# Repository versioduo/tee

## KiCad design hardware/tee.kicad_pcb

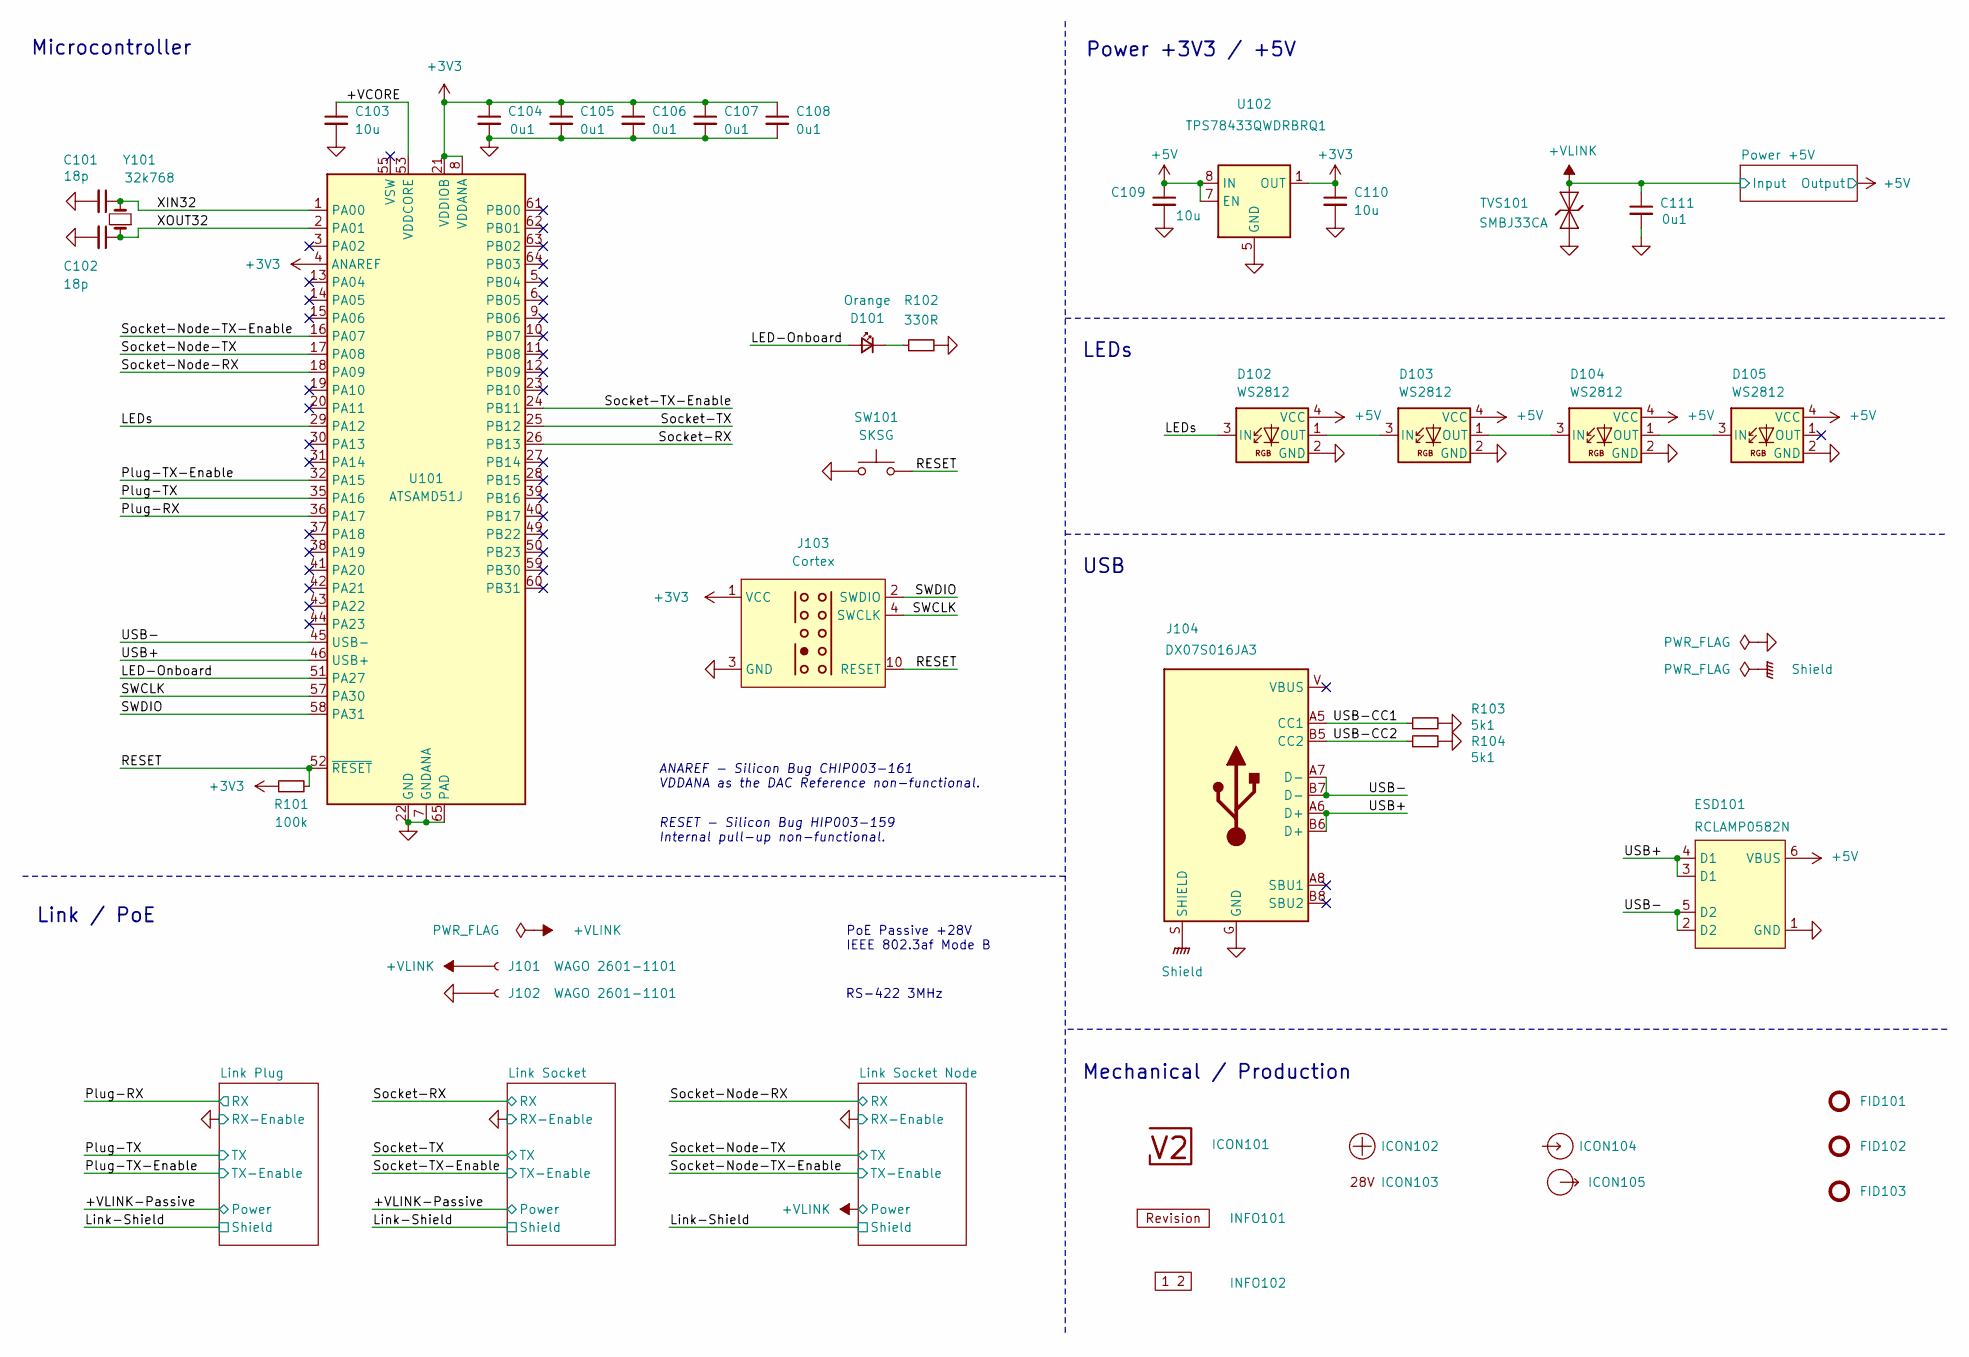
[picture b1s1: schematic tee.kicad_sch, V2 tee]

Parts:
C101, C102: 18p; C_1608; Rating 50V; Mouser 810-CGA3E2C0G1H180J
C103: 10u; C_1608; Rating 10V; Mouser 810-C1608X6S1A106M
C104, C105, C106, C107, C108, C111: 0u1; C_1608; Rating 50V; Mouser 810-CGA3E2X7R1H104MA
C109, C110: 10u; C_2012; Rating 25V; Mouser 810-C2012X5R1E106K
D101: Orange; LED_1608; Rating 605nm; Mouser 755-SML-D12D1WT86
D102, D103, D104, D105: WS2812; WS2812-2020; Rating 15mA; LCSC C965555
ESD101: RCLAMP0582N; SLP1210N6; Rating 20kV; Mouser 947-RCLAMP0582N.TCT
FID101, FID102, FID103: Fiducial_Paste; Fiducial_0.5mm_Mask1mm_Paste
ICON101: V2-logo; Logo_Small
ICON102: Plus; Plus_Small
ICON103: 28V
ICON104: Arrow_In
ICON105: Arrow_Out
INFO101: Revision
INFO102: Layer_Numbers-4
J101, J102: WAGO 2601-1101; 2601-1101; Rating 17.5A
J103: Cortex
J104: DX07S016JA3; JAE_DX07S016JA3; Rating USB2.0; Mouser 656-DX07S016JA3R1500
R101: 100k; R_1608; Rating 100mW; Mouser 71-CRCW0603100KFKEAC
R102: 330R; R_1608; Rating 100mW; Mouser 71-CRCW0603330RFKEAC
R103, R104: 5k1; R_1608; Rating 100mW; Mouser 71-CRCW06035K10FKEAC
SW101: SKSG; Rating 1.6N; Mouser 688-SKSGACE010
TVS101: SMBJ33CA; D_SMB; Rating 33V; Mouser 652-SMBJ33CA-Q
U101: ATSAMD51J; QFN-64-1EP_9x9mm_P0.5mm_EP4.8x4.8mm_ThermalVias; Rating Cortex-M4F; Mouser 556-ATSAMD51J19AMU
U102: TPS78433QWDRBRQ1; VSON-8-1_3x3mm_P0.65_EP1.65x2.4mm; Rating 300mA; Mouser 595-TPS78433QWDRBRQ1
Y101: 32k768; Crystal_SMD_3215-2Pin_3.2x1.5mm; Rating 10ppm; Mouser 815-ABS0716632.768KT

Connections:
+3V3: C104.1, C105.1, C106.1, C107.1, C108.1, C110.1, J103.1 (VCC), R101.1, U101.4 (ANAREF), U101.8 (VDDANA), U101.21 (VDDIOB), U101.34 (VDDIO), U101.48 (VDDIO), U101.56 (VDDIO), U102.1 (OUT); also elsewhere on the board
+5V: C109.1, D102.4 (VCC), D103.4 (VCC), D104.4 (VCC), D105.4 (VCC), ESD101.6 (VBUS), U102.7 (EN), U102.8 (IN); also elsewhere on the board
/+VCORE: C103.1, U101.53 (VDDCORE)
/+VLINK: C111.1, J101.1, TVS101.2 (A); also elsewhere on the board
/LED-Onboard: D101.2 (A), U101.51 (PA27)
/LEDs: D102.3 (IN), U101.29 (PA12)
/Plug-RX: U101.36 (PA17); also elsewhere on the board
/Plug-TX: U101.35 (PA16); also elsewhere on the board
/Plug-TX-Enable: U101.32 (PA15); also elsewhere on the board
/RESET: J103.10 (RESET), R101.2, SW101.2, U101.52 (~RESET)
/SWCLK: J103.4 (SWCLK), U101.57 (PA30)
/SWDIO: J103.2 (SWDIO), U101.58 (PA31)
/Shield: J104.S (SHIELD)
/Socket-Node-RX: U101.18 (PA09); also elsewhere on the board
/Socket-Node-TX: U101.17 (PA08); also elsewhere on the board
/Socket-Node-TX-Enable: U101.16 (PA07); also elsewhere on the board
/Socket-RX: U101.26 (PB13); also elsewhere on the board
/Socket-TX: U101.25 (PB12); also elsewhere on the board
/Socket-TX-Enable: U101.24 (PB11); also elsewhere on the board
/USB+: ESD101.3 (D1), ESD101.4 (D1), J104.A6 (D+), J104.B6 (D+), U101.46 (USB+)
/USB-: ESD101.2 (D2), ESD101.5 (D2), J104.A7 (D-), J104.B7 (D-), U101.45 (USB-)
/USB-CC1: J104.A5 (CC1), R103.1
/USB-CC2: J104.B5 (CC2), R104.1
/XIN32: C101.1, U101.1 (PA00), Y101.2
/XOUT32: C102.1, U101.2 (PA01), Y101.1
GND: C101.2, C102.2, C103.2, C104.2, C105.2, C106.2, C107.2, C108.2, C109.2, C110.2, C111.2, D102.2 (GND), D103.2 (GND), D104.2 (GND), D105.2 (GND), ESD101.1 (GND), J102.1, J103.3 (GND), J103.5 (GND), J104.G (GND), R102.2, R103.2, R104.2, SW101.1, TVS101.1 (K), U101.7 (GNDANA), U101.22 (GND), U101.33 (GND), U101.47 (GND), U101.54 (GND), U101.65 (PAD), U102.5 (GND), U102.9 (GND); also elsewhere on the board
unnamed: D101.1 (K), R102.1
unnamed: D102.1 (OUT), D103.3 (IN)
unnamed: D103.1 (OUT), D104.3 (IN)
unnamed: D104.1 (OUT), D105.3 (IN)

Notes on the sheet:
ANAREF - Silicon Bug CHIP003-161 VDDANA as the DAC Reference non-functional.
Link / PoE
RESET - Silicon Bug HIP003-159 Internal pull-up non-functional.
LEDs
Power +3V3 / +5V
Mechanical / Production
RS-422 3MHz
Microcontroller
PoE Passive +28V IEEE 802.3af Mode B
USB

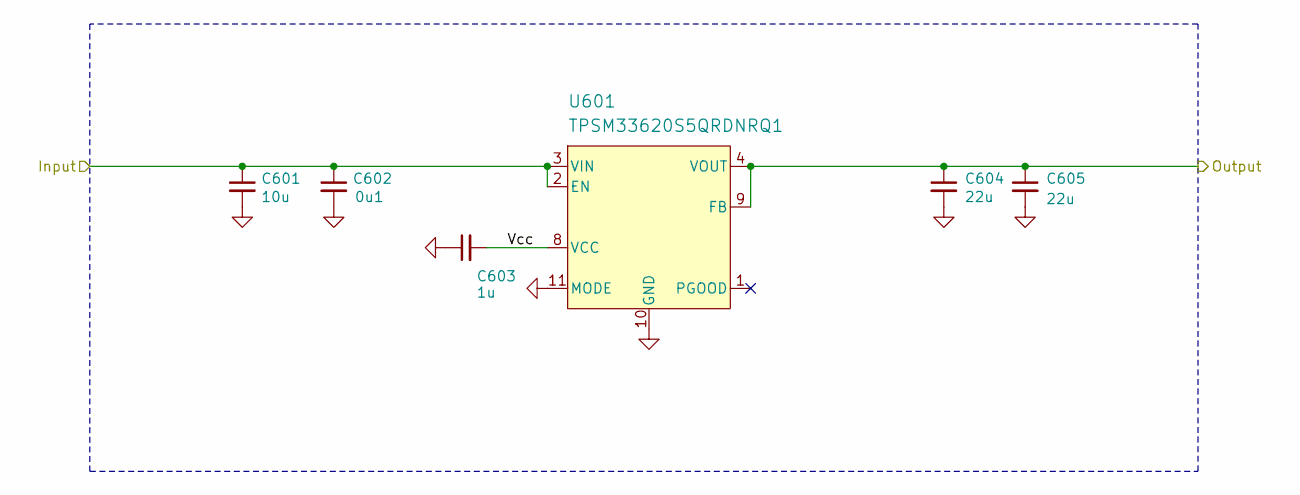
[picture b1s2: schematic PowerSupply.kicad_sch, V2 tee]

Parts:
C601: 10u; C_3225; Rating 50V; Mouser 810-CNC6P1X7R1H106K2
C602: 0u1; C_1608; Rating 50V; Mouser 810-CGA3E2X7R1H104MA
C603: 1u; C_1608; Rating 50V; Mouser 810-CGA3E3X7R1H105K0
C604, C605: 22u; C_3225; Rating 25V; Mouser 810-CGA6P3X7R1E226M5
U601: TPSM33620S5QRDNRQ1; QFN-11; Rating 2A; Mouser 595-SM33620S5QRDNRQ1

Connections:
+5V: C604.1, C605.1, U601.4 (VOUT), U601.9 (FB); also elsewhere on the board
/+VLINK: C601.1, C602.1, U601.2 (EN), U601.3 (VIN); also elsewhere on the board
/Power +5V/Vcc: C603.2, U601.8 (VCC)
GND: C601.2, C602.2, C603.1, C604.2, C605.2, U601.10 (GND), U601.11 (MODE); also elsewhere on the board

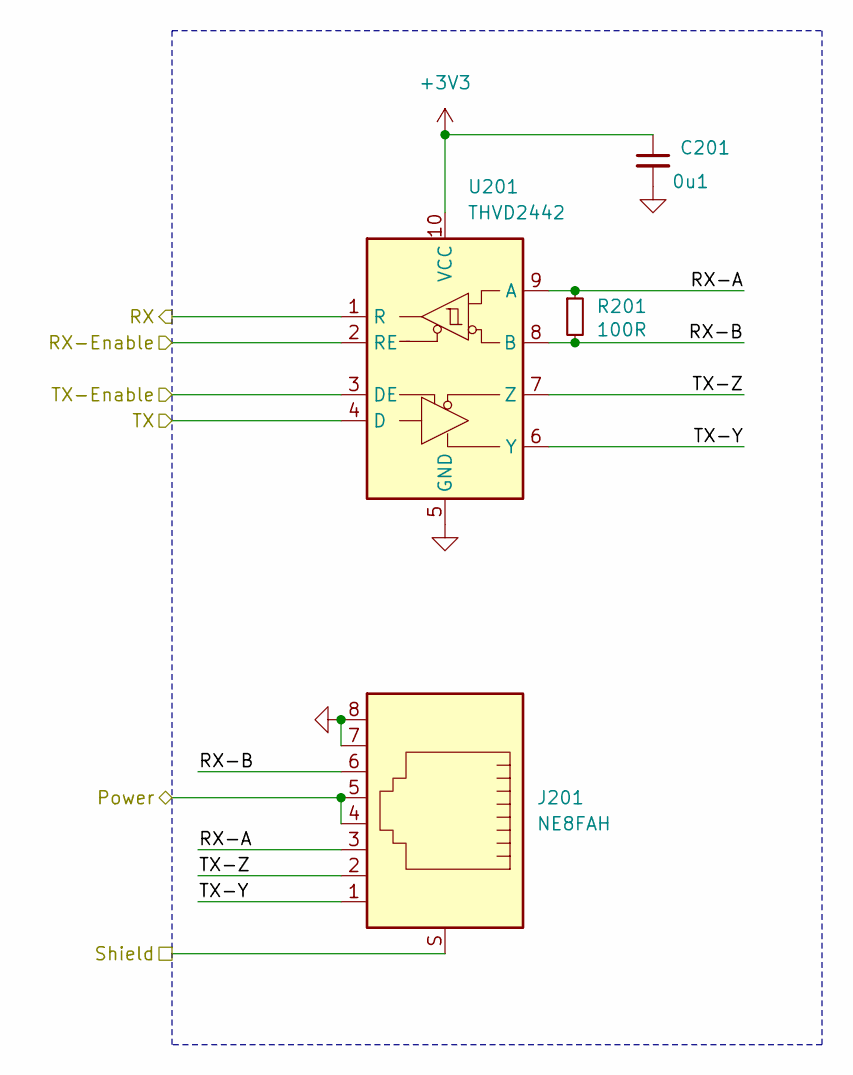
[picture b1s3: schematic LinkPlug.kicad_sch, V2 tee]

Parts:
C201: 0u1; C_1608; Rating 50V; Mouser 810-CGA3E2X7R1H104MA
J201: NE8FAH; Rating CAT5e; Mouser 568-NE8FAH
R201: 100R; R_1608; Rating 330mW; Mouser 71-CRCW0603100RFKEAH
U201: THVD2442; VSON-10-4-1EP_3x3mm_P0.5mm_EP1.65x2.4mm_ThermalVias; Rating 20Mbps; Mouser 595-THVD2442DRCR

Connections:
+3V3: C201.1, U201.10 (VCC); also elsewhere on the board
/+VLINK-Passive: J201.4, J201.5; also elsewhere on the board
/Link Plug/RX-A: J201.3, R201.1, U201.9 (A)
/Link Plug/RX-B: J201.6, R201.2, U201.8 (B)
/Link Plug/TX-Y: J201.1, U201.6 (Y)
/Link Plug/TX-Z: J201.2, U201.7 (Z)
/Link-Shield: J201.S; also elsewhere on the board
/Plug-RX: U201.1 (R); also elsewhere on the board
/Plug-TX: U201.4 (D); also elsewhere on the board
/Plug-TX-Enable: U201.3 (DE); also elsewhere on the board
GND: C201.2, J201.7, J201.8, U201.2 (RE), U201.5 (GND), U201.11 (GND); also elsewhere on the board

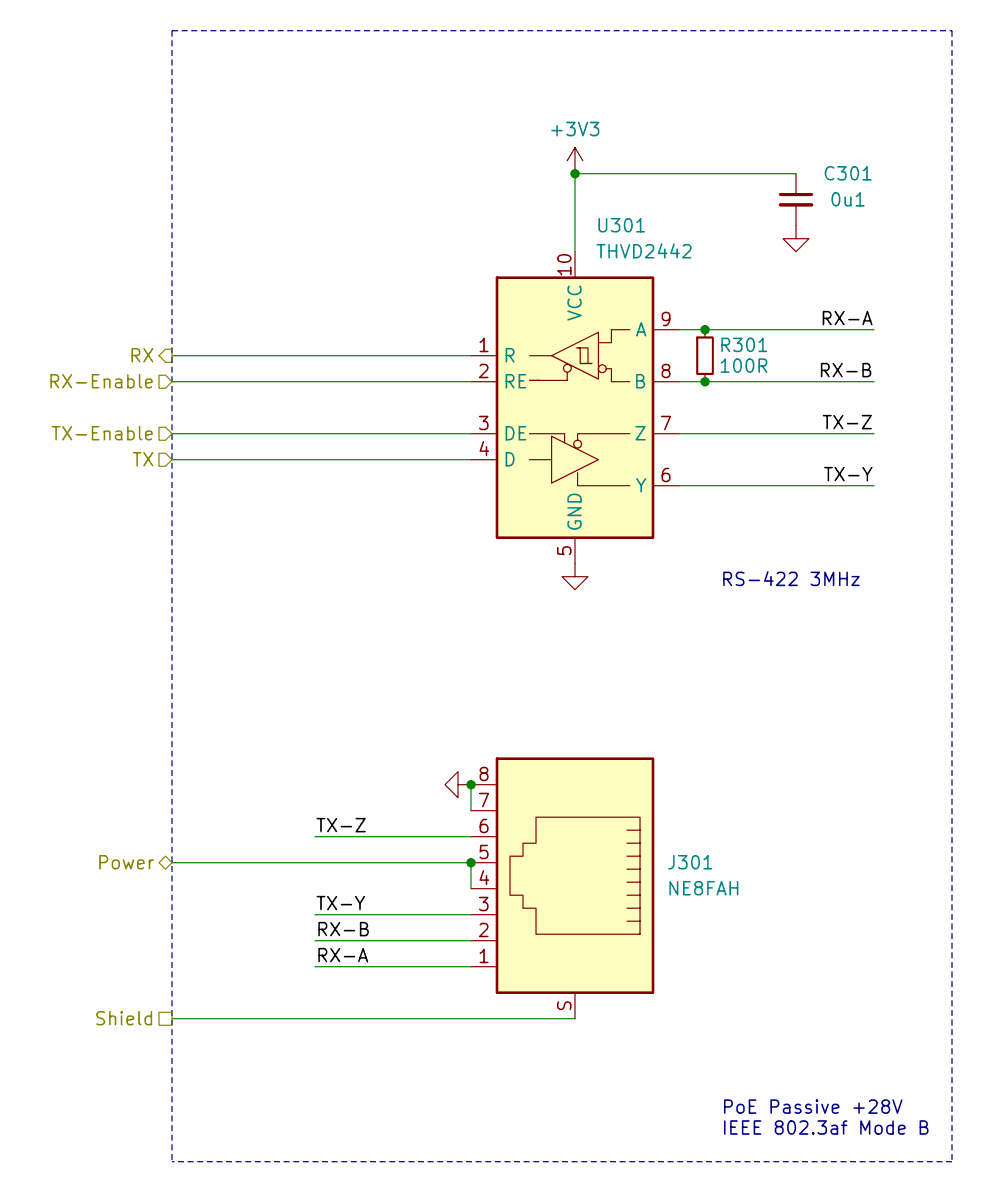
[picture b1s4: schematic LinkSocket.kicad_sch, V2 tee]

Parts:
C301: 0u1; C_1608; Rating 50V; Mouser 810-CGA3E2X7R1H104MA
J301: NE8FAH; Rating CAT5e; Mouser 568-NE8FAH
R301: 100R; R_1608; Rating 330mW; Mouser 71-CRCW0603100RFKEAH
U301: THVD2442; VSON-10-4-1EP_3x3mm_P0.5mm_EP1.65x2.4mm_ThermalVias; Rating 20Mbps; Mouser 595-THVD2442DRCR

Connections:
+3V3: C301.1, U301.10 (VCC); also elsewhere on the board
/+VLINK-Passive: J301.4, J301.5; also elsewhere on the board
/Link Socket/RX-A: J301.1, R301.1, U301.9 (A)
/Link Socket/RX-B: J301.2, R301.2, U301.8 (B)
/Link Socket/TX-Y: J301.3, U301.6 (Y)
/Link Socket/TX-Z: J301.6, U301.7 (Z)
/Link-Shield: J301.S; also elsewhere on the board
/Socket-RX: U301.1 (R); also elsewhere on the board
/Socket-TX: U301.4 (D); also elsewhere on the board
/Socket-TX-Enable: U301.3 (DE); also elsewhere on the board
GND: C301.2, J301.7, J301.8, U301.2 (RE), U301.5 (GND), U301.11 (GND); also elsewhere on the board

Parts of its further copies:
C401: 0u1; C_1608; Rating 50V; Mouser 810-CGA3E2X7R1H104MA
J401: NE8FAH; Rating CAT5e; Mouser 568-NE8FAH
R401: 100R; R_1608; Rating 330mW; Mouser 71-CRCW0603100RFKEAH
U401: THVD2442; VSON-10-4-1EP_3x3mm_P0.5mm_EP1.65x2.4mm_ThermalVias; Rating 20Mbps; Mouser 595-THVD2442DRCR

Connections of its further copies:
+3V3: C401.1, U401.10 (VCC); also elsewhere on the board
/+VLINK: J401.4, J401.5; also elsewhere on the board
/Link Socket Node/RX-A: J401.1, R401.1, U401.9 (A)
/Link Socket Node/RX-B: J401.2, R401.2, U401.8 (B)
/Link Socket Node/TX-Y: J401.3, U401.6 (Y)
/Link Socket Node/TX-Z: J401.6, U401.7 (Z)
/Link-Shield: J401.S; also elsewhere on the board
/Socket-Node-RX: U401.1 (R); also elsewhere on the board
/Socket-Node-TX: U401.4 (D); also elsewhere on the board
/Socket-Node-TX-Enable: U401.3 (DE); also elsewhere on the board
GND: C401.2, J401.7, J401.8, U401.2 (RE), U401.5 (GND), U401.11 (GND); also elsewhere on the board

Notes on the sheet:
PoE Passive +28V IEEE 802.3af Mode B
RS-422 3MHz

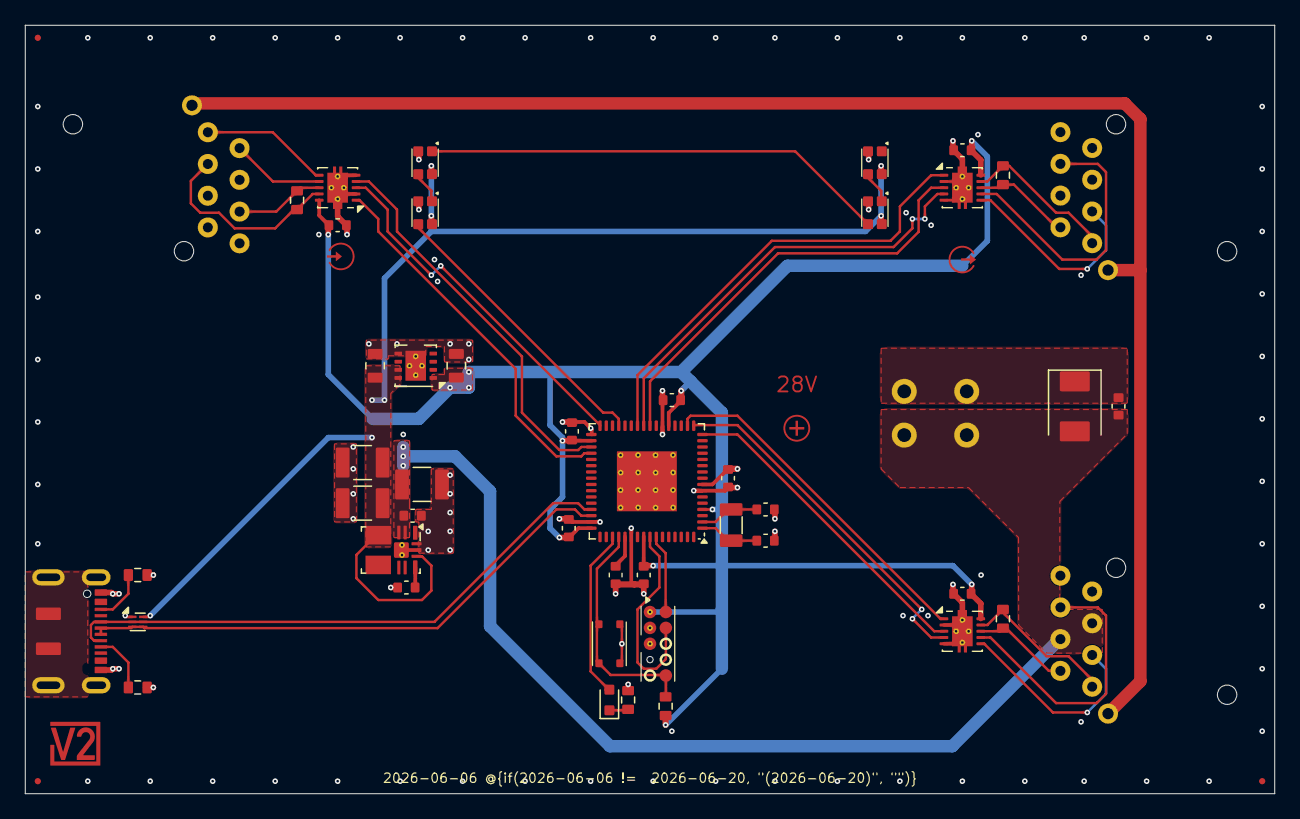
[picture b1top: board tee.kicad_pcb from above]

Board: 4 copper layers, 100.0 x 61.5 mm, 58 parts (0 on the bottom side), 44 nets.
